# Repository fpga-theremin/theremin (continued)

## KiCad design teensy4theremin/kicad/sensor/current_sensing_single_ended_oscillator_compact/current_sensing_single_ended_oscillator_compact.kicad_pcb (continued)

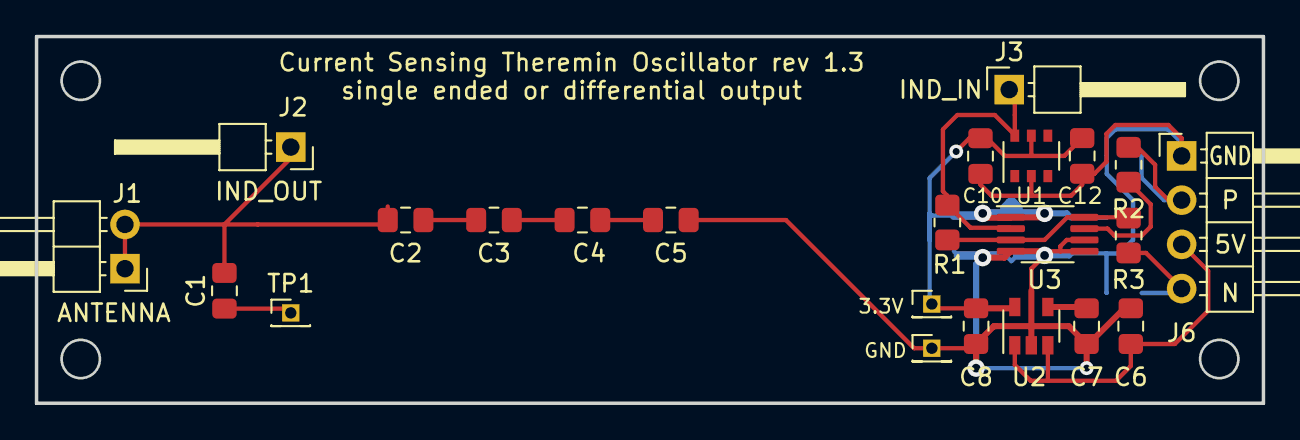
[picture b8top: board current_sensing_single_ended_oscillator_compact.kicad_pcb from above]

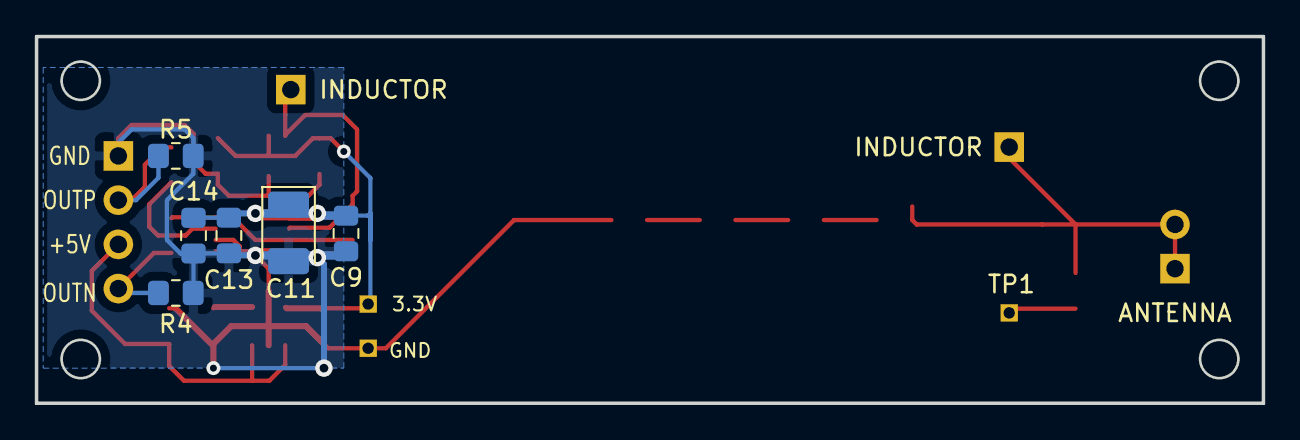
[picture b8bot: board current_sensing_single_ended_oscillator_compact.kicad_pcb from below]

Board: 2 copper layers, 70.5 x 21.1 mm, 29 parts (6 on the bottom side), 14 nets.

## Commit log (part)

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2019-08-12 axi4 periph
2019-08-13 theremin io ip
2019-08-13 buttons input mux
2019-08-13 refactor source dirs
2019-08-13 refactor dirs
2019-08-13 drivers stub
2019-08-13 fixes
2019-08-13 fix routing conflict
2019-08-13 block design screenshot
2019-08-13 device screenshot
2019-08-14 block design
2019-08-15 rgb led interface; iserdes placement
2019-08-15 axi slave test bench and fixes
2019-08-15 fix axi slave
2019-08-15 ip driver
2019-08-16 fix LED pwm
2019-08-19 move audio irq to different register, add subsample and sample counters
2019-08-19 update block design
2019-08-19 update IP
2019-08-19 update hardware
2019-08-20 update hdl
2019-08-20 add SDK
2019-08-22 update hw design
2019-08-22 initial simulator
2019-08-22 sdk commit
2019-08-22 add libs
2019-08-23 refactor pwm
2019-08-23 lcd screens connected
2019-08-23 simulator, continue
2019-08-23 simulator - audio playback
2019-08-23 cleanup
2019-09-02 lcd screen; simulator
2019-09-02 fill rect 32bit optimization
2019-09-02 mouse
2019-09-02 encoders rotation, button state duration
2019-09-02 encoders and buttons rework
2019-09-02 encoder reg widget
2019-09-02 regs display
2019-09-02 sensor convertor
2019-09-03 linearization
2019-09-03 note to frequency and phase shift conversion
2019-09-03 synth in sim
2019-09-03 simple synth working in simulator
2019-09-03 sin table
2019-09-03 sin interpolation tables
2019-09-03 fixes:
2019-09-04 integer synth
2019-09-04 additive synth working
2019-09-04 synth control refactor
2019-09-04 synth control
2019-09-04 fixes for xil sdk
2019-09-05 pipe monster photo
2019-09-05 cabinet - pipe monster photo added
2019-09-05 fonts, lines
2019-09-05 formants
2019-09-05 remove hdf
2019-09-06 replace fonts
2019-09-06 lcd images
2019-09-06 rename image
2019-09-06 update - LCD is working!
2019-09-09 ugui, part 1
2019-10-09 schematics
2019-10-10 sensor schematic update
2019-10-10 ltspice model - teensy
2019-10-10 sim result
2019-10-10 simulation results
2019-10-10 ltspice model v3
2019-10-10 model v3
2019-10-10 antenna voltage
2019-10-14 sensor pcb 3d view
2019-10-15 new simulation plots - linear distance steps
2019-10-15 board images
2019-10-18 5V phase shift sensor
2019-11-05 opamp lc oscillator and quadrant heterodyne
2019-11-05 quadrant heterodyne ltspice simulation images
2019-11-08 opamp oscillator kicad
2019-11-12 sine oscillator proto PCB
2019-11-12 sine oscillator proto pcb 3d render
2019-11-12 sine oscillator SMD pcb
2019-11-12 oscillator PCB
2019-11-12 update sensor pcb
2019-11-12 update oscillator smd pcb 3d render
2019-11-14 update ltspice simulations - phase shift
2019-11-15 update phase shift
2019-11-15 phase shift sensor
2019-11-15 phase shit sensor
2019-11-16 simulation
2019-11-16 coil lc meter
2019-11-18 update phase shift sensor model
2019-11-18 LTSpice simulation of phase shift sensor
2019-11-18 phase shift pcb kicad proto
2019-11-18 phase shift sensor PCB
2019-11-18 phase shift sensor pcb 3d render
2019-11-19 paradox mixer
2019-11-19 mixer experiments
2019-11-19 library template
2019-11-19 simulator template
2019-11-19 cleanup fpga code from simulator
2019-11-19 teensy4 theremin simulator
2019-11-20 PhaseShift library development in progress:
2019-11-21 add component spice models
2019-11-21 paradox mixer images
2019-11-22 kicad schematics for wavetable synth
2019-11-22 input capture is working
2019-11-23 RC sensor
2019-11-24 update phase shift library for teensy4
2019-11-24 git ignore - add LTSpice files
2019-11-25 sensor
2019-11-25 optimized simplified LC phase shift sensor, additional model for 1.2mH 0.2mm wire coil
2019-11-25 phase shift sensor simple schematic
2019-11-25 phase shift sensor ltspice images
2019-11-25 simple phase shift sensor
2019-11-25 phase shift sensor proto - simple
2019-11-25 sensor PCB update
2019-11-25 add phase shift simple sensor kicad images
2019-11-25 update sensor model - add centering and protective resistors
2019-11-25 add 74hc74 model
2019-11-25 update schematics
2019-11-25 sensor PCB all layers
2019-11-25 update phase shift sensor schematics
2019-11-26 update sensor schematic
2019-11-26 update phase shift sensor prototype PCB
2019-11-26 update:
2019-11-27 phase shift sensor update
2019-11-27 phase shift ltspice simulation
2019-11-27 update LTSpice model of phase shift sensor
2019-11-27 update prototype phase sensor board
2019-11-27 phase shift sensor prototype board pcb
2019-11-27 update phase shift sensor prototype PCB - change connector to 5-pin one, with additional ground
2019-11-27 update sensor PCB images with new connector
2019-11-27 SMD version of phase shift sensor
2019-11-27 SMD version of sensor - 3d render of PCB
2019-11-27 LTSpice model with 0.1mm air core inductor 4mH
2019-11-28 spice model - better q
2019-11-28 phase shift sensor models - trying to optimize
2019-12-02 sensor board
2019-12-03 sensor proto pcb
2019-12-05 sensor simulation
2019-12-06 update kicad project
2019-12-09 phase shift sensor PCB and simulation
2019-12-09 update phase shift lib test sketch
2019-12-10 proto pcb - fix 3v3 voltage reg pins
2019-12-10 pipe monster photos
2019-12-10 sensor PCB connections in pipe monster v4
2019-12-10 cabinet mounting
2019-12-10 update sensor pcb - 3v3 regulator
2019-12-10 sensor pcb - gerber files, order 1
2019-12-10 sensor pcb order 1 gerber drawing
2020-02-10 phase shift sensor modelling
2020-02-11 phase shift sensor schematic - 0.125 mm wire simulation
2020-02-13 sensor board, 3.3V optional double regulators
2020-02-14 phase shift sensor - new
2020-02-17 osc simulation
2020-02-18 oscillator model
2020-02-18 oscillator - KiCAD project
2020-02-18 add oscillator gerber files
2020-02-18 analog switch heterodyne KiCad project
2020-02-18 update pcb
2020-02-18 heterodyne pcb
2020-02-19 analog switch heterodyne PCB and gerber
2020-02-19 new sensor and heterodyne images
2020-02-20 use adg721 spice model in simulation of mixer
2020-02-20 gerber view - oscillator and mixer
2020-02-20 mixer simulation
2020-02-21 xor sensor verilog code, part 1
2020-02-21 update - support option for 1 or 2 phases generation
2020-02-21 sv code - oversampling frequency gen
2020-02-23 theremin sensor simulation
2020-02-24 update sensor simulation
2020-02-24 sensor sim updated
2020-02-24 sensor diagram
2020-02-24 filter performance stats
2020-02-24 FIR filter window - linear
2020-02-25 sensor sim
2020-02-25 update sim
2020-02-25 sensor simulator
2020-02-26 IIR filter in sensor sim
2020-02-26 floating point calculation in sensor sim
2020-02-26 zoom bad point error - sensor sim
2020-02-26 sensor simulation results
2020-02-26 rebuild pages
2020-02-27 bit length
2020-02-27 simulation results - available bits
2020-03-02 simulator - CMake files
2020-03-02 teensy theremin simulator, LCD
2020-03-03 oversampling sensor vivado project
2020-03-03 add delay diff filter
2020-03-04 theremin sensor - frequency measure modules
2020-03-04 fir filter
2020-03-05 theremin sensor fpga - iir filter
2020-03-06 main hum noise analysis
2020-03-08 plywood cabinet cora
2020-03-08 main hum noise - part 1
2020-03-09 remove unused files from sensor fpga impl
2020-03-09 edge to pulse position converter and clock domain adapter
2020-03-09 theremin sensor top level (excluding AXI peripherial level)
2020-03-09 sensor module - IIR added
2020-03-09 fix IIR output
2020-03-10 bcpu
2020-03-10 bcpu ALU
2020-03-10 bcpu alu working
2020-03-11 bcpu ALU universal implementation added
2020-03-11 bcpu ALU fixes
2020-03-11 update bcpu
2020-03-12 regfile for bcpu
2020-03-12 bcpu regfile
2020-03-12 bcpu instruction decoder
2020-03-12 bcpu dual port BRAM impl
2020-03-13 update bcpu, add instruction counter registers impl
2020-03-13 bcpu memory ops implementation
2020-03-13 notes{
2020-03-13 notes
2020-03-16 bus operations
2020-03-16 bus op for bcpu
2020-03-17 bcpu bus op resource optimization
2020-03-17 bcpu core initial implementation
2020-03-17 bcpu core
2020-03-17 bcpu alu testbench
2020-03-18 bcpu - alu rework
2020-03-26 bcpu refactor
2020-07-21 bcpu16 - rework of 16bit barrel cpu - 18bit instruction - 8 regs
2020-07-31 bcpu16 - integrated
2020-08-29 inverter oscillator images
2020-08-29 update image
2020-09-19 theremin sensor teensy4 pwm dma
2020-09-19 teensy4 theremin sensor experiment results
2020-09-21 bridged oscillator ltspice model
2020-09-21 captured data analysis
2020-09-21 npn osc schematic
2020-09-21 lt spice models of oscillator
2020-09-22 oscillator optimization
2020-09-22 updated ltspice model of oscillator
2020-09-23 new oscillator schematics images
2020-09-23 kicad schematics of npn-pnp colpitts oscillator
2020-09-23 submit gerber files
2020-10-02 teensy 4 theremin pcbs, initial version
2020-10-02 main board pcb
2020-10-02 PCB placement screenshots
2020-10-06 main boark kicad
2020-10-06 main board
2020-10-06 props
2020-10-07 update pcb images
2020-10-13 teensy theremin images
2020-10-14 display controls board
2020-10-14 main pcb fixes
2020-10-14 npn and npn-pnp oscillator models comparision
2020-10-14 oscillator ltspice models
2020-10-14 teensy 41 theremin main board and display board rev 0.1
2020-10-15 LTSpice model:
2020-10-15 ltspice model of oscillator
2020-10-15 single npn noise data
2020-10-15 npn oscillator noise data images
2020-10-16 colpitts bridge osc
2020-10-18 ltspice model filter and output buffers
2020-10-18 sensor ltspice model with filter and buffers
2020-10-19 noise model
2020-10-21 current sensing based oscillator with bandpass filter
2020-10-21 ltspice current sensing oscillator model
2020-10-22 current sensing oscillator - simple
2020-10-22 sensor images
2020-10-22 rename
2020-10-23 sensor pcb
2020-10-23 current sensing pcb - kicad
2020-10-23 current sensing single ended oscillator kicad project
2020-10-23 single ended oscillator pcb
2020-10-24 sensor compact pcb
2020-10-24 current sensting single ended compact pcb
2020-10-24 update gerber files
2020-10-24 update oscillator pcb
2020-10-24 oscillator pcb images update
2020-10-30 update sensor
2020-10-30 pcbs
2020-10-30 spice model of sine diff out oscillator
2020-10-30 sine filter model
2020-11-05 oscillator
2020-11-06 inductive current sensing model
2020-11-06 oscillator models
2020-11-08 oscillators ltspice
2020-11-08 oscillator ltspice
2020-11-08 update display and control board images
2020-11-08 update PCBs
2020-11-10 cora z7 theremin dual 100MHz ADC pmods board
2020-11-11 update ADC board pcb, replace ssop20 footprint
2020-11-16 oscillators
2020-11-16 teensy theremin main board, v2
2020-11-16 sensor model
2020-12-09 lt1711 sensor
2020-12-10 oscillators ltspice models
2020-12-10 current sensing npn pnp oscillator
2020-12-10 update oscillator
2020-12-12 oscillator - dewster, optimized
2020-12-24 ltspice models:
2020-12-24 ltspice oscillator model:
2020-12-24 update schematic
2020-12-24 test photos
2020-12-25 BJT current sensing oscillator kicad project
2020-12-25 update model
2020-12-25 current sensing sensor
2020-12-25 update sensor schematics and model:
2020-12-28 update test analysis
2020-12-30 pll oscillator
2021-05-13 add images
2021-05-18 z7lite
2021-05-18 theremin kicad files
2021-05-18 pcb render - z7 lite main board
2021-05-20 controls pcb renders
2021-05-21 controls board pcb
2021-05-21 pcbs updated, jlcpcb prod rev 0.1, gerber files
2021-05-21 add z7 lite boards schematics
2021-05-21 sensor schematic
2021-06-01 theremin sensor PLL implementation, basic blocks
2021-06-09 pll diagram
2021-06-09 sensor PLL
2021-06-09 update diagram:
2021-06-09 LP IIR filter
2021-06-10 iir lowpass filter - fixed
2021-06-11 pcb images
